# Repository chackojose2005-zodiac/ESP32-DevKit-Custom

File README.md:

# ESP32 Development Kit — Custom PCB Design

> A 4-layer KiCad PCB clone of the Espressif ESP32-DevKitC-v4, designed from the official reference schematic.

---

## Table of Contents

- [Overview](#overview)
- [Board Specifications](#board-specifications)
- [Schematic & Design Details](#schematic--design-details)
- [Bill of Materials (BOM)](#bill-of-materials-bom)
- [Layer Stack-Up](#layer-stack-up)
- [Repository Structure](#repository-structure)
- [How to Open in KiCad](#how-to-open-in-kicad)
- [How to Order the PCB](#how-to-order-the-pcb)
- [Design Notes & Customizations](#design-notes--customizations)
- [References](#references)
- [Author](#author)

---

## Overview

This project is a custom clone of the **Espressif ESP32-DevKitC-v4** development board, designed entirely in **KiCad**. The design is based on the official Espressif reference schematic and layout, with minor modifications for ease of hand assembly.

The board features:
- **ESP32-WROOM-32D** module with integrated PCB antenna
- **CP2102N** USB-to-UART bridge for serial programming
- **AMS1117-3.3** LDO voltage regulator (3.3 V output)
- **BOOT** and **EN** push buttons
- **2 × 19-pin** header connectors exposing all GPIO pins
- SMD components on both front and back copper layers

**Board Dimensions:** 30.73 mm × 56.90 mm  
**Layer Count:** 4 layers  
**Form Factor:** Matches the original ESP32-DevKitC-v4

---

## Board Specifications

| Parameter            | Value                        |
|----------------------|------------------------------|
| Microcontroller      | ESP32-WROOM-32D              |
| USB-UART Bridge      | CP2102N-A01-GQFN28           |
| Voltage Regulator    | AMS1117-3.3 (SOT-223)        |
| Input Voltage        | 5 V via Micro-USB            |
| Output Voltage       | 3.3 V regulated              |
| GPIO Headers         | 2 × 19-pin, 2.54 mm pitch    |
| Board Layers         | 4 (Signal / Signal / Signal / Signal) |
| Board Dimensions     | 30.73 mm × 56.90 mm          |
| Component Standard   | SMD (0402 / 0603 packages)   |
| KiCad Version        | KiCad 7 / 8                  |

---

## Schematic & Design Details

The schematic is organized into **five functional blocks**, mirroring the Espressif reference design:

1. **Power Supply** — Micro-USB input → AMS1117-3.3 LDO → 3.3 V rail with decoupling capacitors
2. **USB / USB-UART** — CP2102N bridge with ESD protection diodes (D4, D5, D6) and auto-reset circuit
3. **ESP32 Module** — ESP32-WROOM-32D with all GPIO broken out to headers
4. **Switch Buttons** — BOOT (GPIO0) and EN (chip enable) with RC debounce networks
5. **Connectors** — J2 and J3 (2 × 19-pin headers)

The auto-reset circuit uses two **MMSS8050** NPN transistors (Q1, Q2) driven by the CP2102N's RTS and DTR lines. This allows the Arduino IDE and `esptool.py` to reset and flash the ESP32 without pressing buttons manually.

---

## Bill of Materials (BOM)

| Reference              | Value              | Footprint                                      |
|------------------------|--------------------|------------------------------------------------|
| C1, C2, C21            | 22 µF / 10 V (20%) | Capacitor_SMD:C_0201_0603Metric                |
| C9, C14, C19, C22      | 0.1 µF / 50 V (10%)| Capacitor_SMD:C_01005_0402Metric               |
| C15                    | 0.1 µF / 50 V (NC) | Capacitor_SMD:C_01005_0402Metric               |
| C20                    | 4.7 µF / 6.3 V     | Capacitor_SMD:C_01005_0402Metric               |
| D1                     | LED                | LED_SMD:LED_0603_1608Metric                    |
| D3                     | Schottky Diode     | Diode_SMD:D_SOD-323                            |
| D4, D5, D6             | TVS Diode          | Diode_SMD:D_SOD-523                            |
| J1                     | USB Micro-B        | Connector_USB:USB_MicroAB_Molex_47590-0001     |
| J2, J3                 | 19-pin Male Header | Connector_PinHeader_2.54mm:PinHeader_1x19_...  |
| MOD1                   | ESP32-WROOM-32D    | ESP32-WROOM32D.pretty:ESP32-WROOM-32D          |
| Q1, Q2                 | MMSS8050-H-TP      | digikey-footprints:SOT-23-3                    |
| R2, R24                | 2 KΩ (5%)          | Resistor_SMD:R_01005_0402Metric                |
| R7, R18                | 0 Ω (5%)           | Resistor_SMD:R_01005_0402Metric                |
| R11, R21, R22          | 10 KΩ (5%)         | Resistor_SMD:R_01005_0402Metric                |
| R23                    | 10 KΩ (NC)         | Resistor_SMD:R_01005_0402Metric                |
| R25                    | 22.1 KΩ (5%)       | Resistor_SMD:R_01005_0402Metric                |
| R26                    | 47.5 KΩ (5%)       | Resistor_SMD:R_01005_0402Metric                |
| SW1, SW2               | Push Button        | Button_Switch_SMD:SW_SPST_B3S-1000             |
| U1                     | CP2102N-A01-GQFN28 | Package_DFN_QFN:TQFN-28-1EP_5x5mm_P0.5mm      |
| U2                     | AMS1117-3.3        | Package_TO_SOT_SMD:SOT-223-3_TabPin2           |

> **(NC)** = Not Connected / DNP (Do Not Populate)

---

## Layer Stack-Up

| Layer      | KiCad Name   | Purpose                     |
|------------|--------------|-----------------------------|
| Layer 1    | F.Cu         | Signal routing (top)        |
| Layer 2    | In1.Cu       | Signal routing (inner 1)    |
| Layer 3    | In2.Cu       | Signal routing (inner 2)    |
| Layer 4    | B.Cu         | Signal routing (bottom)     |

All four copper layers are used for **signal routing**. Power (VCC/3.3 V) and ground (GND) connections are routed as **copper tracks** across all layers using KiCad's **autorouter**, rather than as dedicated power or ground planes. This approach was used to complete all 68 nets with 0 unrouted connections.

> **Note:** In a production design, dedicated inner ground and power planes (In1.Cu = GND, In2.Cu = PWR) are recommended for better RF performance and signal integrity. For this educational clone, autorouted tracks on all four layers achieve full connectivity.

---

## Repository Structure

```
ESP32-DevKit-Custom/
│
├── ESP32-DevKit-Custom.kicad_pro    # KiCad project file
├── ESP32-DevKit-Custom.kicad_sch    # Schematic
├── ESP32-DevKit-Custom.kicad_pcb    # PCB layout
│
├── ESP32-WROOM32D.pretty/           # Custom ESP32-WROOM-32D footprint
├── CP2102N-A01-GQFN28footprint.pretty/ # Custom CP2102N footprint
├── MMSS8050-H-TPfootprint.pretty/   # Custom MMSS8050 footprint
│
├── Gerbers/                         # Manufacturing files
│   ├── ESP32-DevKit-F_Cu.gtl
│   ├── ESP32-DevKit-In1_Cu.g2
│   ├── ESP32-DevKit-In2_Cu.g3
│   ├── ESP32-DevKit-B_Cu.gbl
│   ├── ESP32-DevKit-F_Mask.gts
│   ├── ESP32-DevKit-B_Mask.gbs
│   ├── ESP32-DevKit-F_Silkscreen.gto
│   ├── ESP32-DevKit-B_Silkscreen.gbo
│   ├── ESP32-DevKit-Edge_Cuts.gm1
│   └── ESP32-DevKit-drill.drl
│
├── BOM/
│   └── ESP32-DevKit-BOM.csv         # Bill of materials
│
├── 3D/
│   └── ESP32-DevKit-3D.png          # 3D render screenshot
│
└── README.md
```

---

## How to Open in KiCad

### Prerequisites

- [KiCad 7 or later](https://www.kicad.org/download/) installed
- Internet connection (to download symbol/footprint libraries if missing)

### Steps

1. **Clone this repository:**
   ```bash
   git clone https://github.com/chackojose2005-zodiac/ESP32-DevKit-Custom.git
   cd ESP32-DevKit-Custom
   ```

2. **Open KiCad:**
   Launch KiCad and click **File → Open Project**, then select `ESP32-DevKit-Custom.kicad_pro`.

3. **Open the Schematic:**
   In the KiCad project manager, double-click **Schematic Editor** (`.kicad_sch`) to view the schematic.

4. **Open the PCB Layout:**
   Double-click **PCB Editor** (`.kicad_pcb`) to open the board layout.

5. **Verify the 3D View:**
   In the PCB Editor, go to **View → 3D Viewer** to see the 3D render of the board.

6. **Run DRC (Design Rule Check):**
   In the PCB Editor, go to **Inspect → Design Rules Checker** and click **Run DRC** to verify the design.

---

## How to Order the PCB

### Generating Gerber Files (if not already included)

1. Open the PCB in KiCad PCB Editor.
2. Go to **File → Fabrication Outputs → Gerbers (.gbr)**.
3. Select all layers (F.Cu, In1.Cu, In2.Cu, B.Cu, F.Mask, B.Mask, F.Silkscreen, B.Silkscreen, Edge.Cuts).
4. Click **Plot**.
5. Also generate drill files: **File → Fabrication Outputs → Drill Files (.drl)**.
6. Zip the entire `Gerbers/` folder.

### Ordering from JLCPCB (Recommended)

1. Go to [jlcpcb.com](https://jlcpcb.com) and click **Order Now**.
2. Upload the zipped Gerber files.
3. Set the following options:
   - **Layers:** 4
   - **Dimensions:** Auto-detected (~30.73 × 56.90 mm)
   - **PCB Quantity:** 5 (minimum)
   - **Surface Finish:** HASL (lead-free) or ENIG
   - **Copper Weight:** 1 oz
4. Review the board preview, then proceed to checkout.

> **Note:** 4-layer boards cost slightly more than 2-layer boards. JLCPCB's 4-layer pricing starts from around $2–5 per board for small quantities.

---

## Design Notes & Customizations

This design is faithful to the Espressif ESP32-DevKitC-v4 reference, with the following intentional modifications:

- **ESP32-WROOM-32D module used** — The design uses the ESP32-WROOM-32D variant with a custom footprint, featuring a single rectangular SMD thermal pad (pad 39) for GND instead of individual through-hole vias.

- **Autorouted PCB layout** — All nets (GND, 3.3 V, signals) are connected using KiCad's autorouter across all four copper layers (F.Cu, In1.Cu, In2.Cu, B.Cu). The result is **0 unrouted connections** across all 68 nets.

- **Voltage regulator (U2 / AMS1117-3.3) placed on the back copper layer (B.Cu)** — In the original Espressif reference, the regulator is on the front. Moving it to the back frees up front-side real estate for small passives, making hand-soldering easier.

- **Custom footprints** — The ESP32-WROOM-32D, CP2102N-A01-GQFN28, and MMSS8050-H-TP footprints were created from scratch and are included in the repository as local `.pretty` libraries.

Other design considerations:
- The ESP32's RF antenna extends **outside** the board edge to avoid copper interference with the 2.4 GHz signal.
- TVS diodes (D4, D5, D6) protect the USB data lines against ESD events.
- RC networks on BOOT and EN pins prevent spurious resets due to contact bounce.

---

## References

- [Espressif ESP32-DevKitC-v4 Reference Design](https://www.espressif.com/en/support/documents/technical-documents?keys=ESP32-Devkit) — Official schematics, PCB layout, BOM, and Gerber files
- [ESP32-WROOM-32D Datasheet](https://www.espressif.com/sites/default/files/documentation/esp32-wroom-32d_esp32-wroom-32u_datasheet_en.pdf)
- [CP2102N Datasheet — Silicon Labs](https://www.silabs.com/documents/public/data-sheets/cp2102n-datasheet.pdf)
- [AMS1117-3.3 Datasheet](http://www.advanced-monolithic.com/pdf/ds1117.pdf)
- [KiCad Documentation](https://docs.kicad.org/)

---

## Author

**Chacko Jose**  
B.Tech Electronics & Communication Engineering, Semester 2  
School of Engineering, CUSAT, Kochi  
GitHub: [@chackojose2005-zodiac](https://github.com/chackojose2005-zodiac)

---

*This project was completed as part of Week 4 — Project 6 of the embedded systems PCB design curriculum.*

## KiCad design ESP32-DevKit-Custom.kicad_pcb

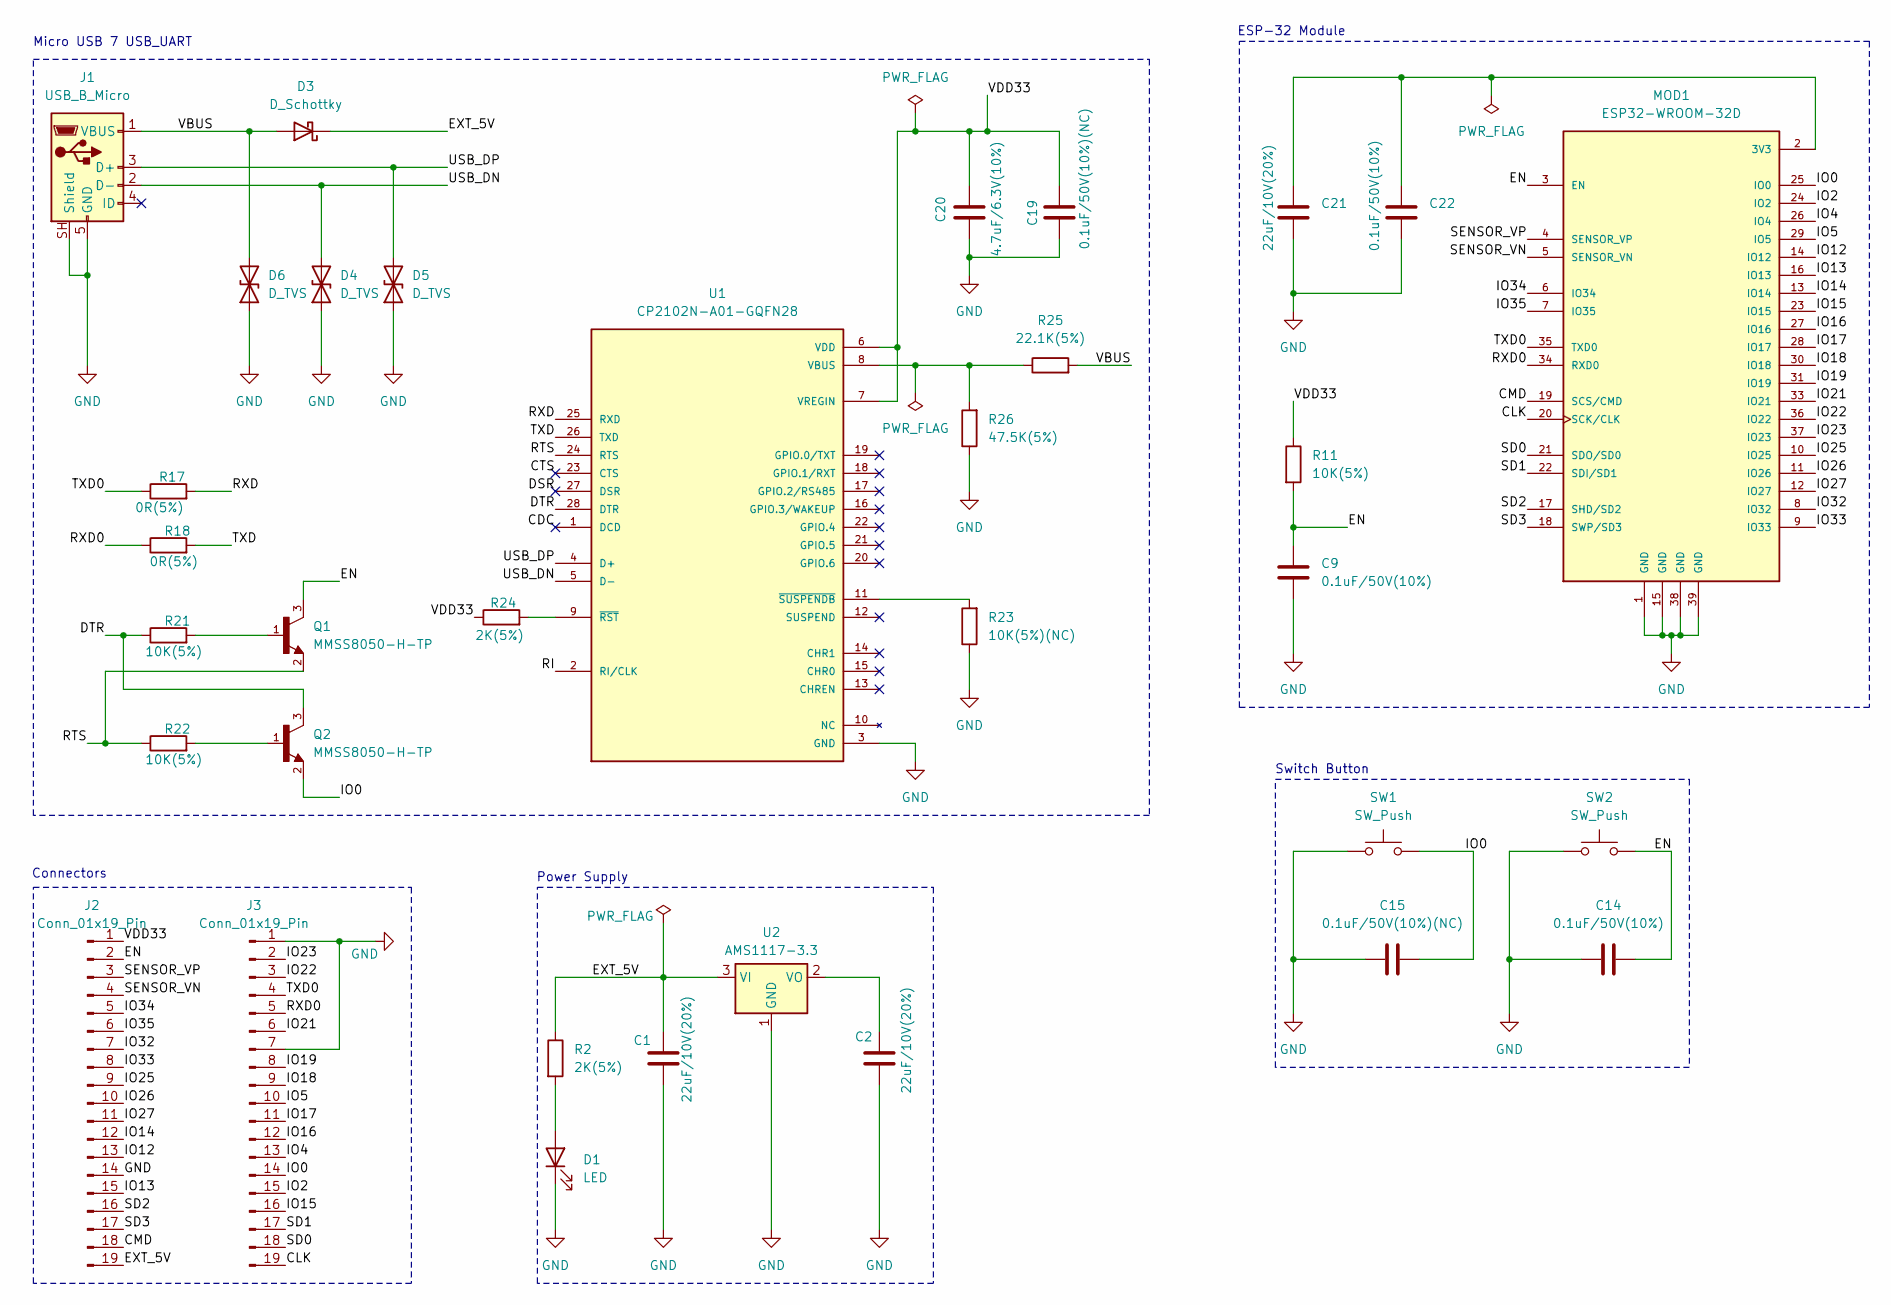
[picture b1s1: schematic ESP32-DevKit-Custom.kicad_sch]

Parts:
C1, C2, C21: 22uF/10V(20%); C_01005_0402Metric
C9, C14, C22: 0.1uF/50V(10%); C_01005_0402Metric
C15, C19: 0.1uF/50V(10%)(NC); C_01005_0402Metric
C20: 4.7uF/6.3V(10%); C_01005_0402Metric
D1: LED; LED_0603_1608Metric
D3: D_Schottky; D_SOD-323
D4, D5, D6: D_TVS; D_SOD-523
J1: USB_B_Micro; USB_Micro-AB_Molex_47590-0001
J2, J3: Conn_01x19_Pin; PinHeader_1x19_P2.54mm_Vertical
MOD1: ESP32-WROOM-32D; MODULE_ESP32-WROOM-32D; PARTREV 1.9
Q1, Q2: MMSS8050-H-TP; TRANS_MMSS8050-H-TP; PARTREV D
R2, R24: 2K(5%); R_01005_0402Metric
R11, R21, R22: 10K(5%); R_01005_0402Metric
R17, R18: 0R(5%); R_01005_0402Metric
R23: 10K(5%)(NC); R_01005_0402Metric
R25: 22.1K(5%); R_01005_0402Metric
R26: 47.5K(5%); R_01005_0402Metric
SW1, SW2: SW_Push; SW_SPST_B3S-1000
U1: CP2102N-A01-GQFN28; QFN50P500X500X80-29N; PARTREV 1.0
U2: AMS1117-3.3; SOT-223-3_TabPin2

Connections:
/CDC: U1.1 (DCD)
/CLK: J3.19, MOD1.20 (SCK/CLK)
/CMD: J2.18, MOD1.19 (SCS/CMD)
/CTS: U1.23 (CTS)
/DSR: U1.27 (DSR)
/DTR: Q2.3, R21.1, U1.28 (DTR)
/EN: C9.1, C14.2, J2.2, MOD1.3 (EN), Q1.3, R11.2, SW2.2
/EXT_5V: C1.1, D3.1 (K), J2.19, R2.1, U2.3 (VI)
/IO0: C15.2, J3.14, MOD1.25 (IO0), Q2.2, SW1.2
/IO2: J3.15, MOD1.24 (IO2)
/IO4: J3.13, MOD1.26 (IO4)
/IO5: J3.10, MOD1.29 (IO5)
/IO12: J2.13, MOD1.14 (IO12)
/IO13: J2.15, MOD1.16 (IO13)
/IO14: J2.12, MOD1.13 (IO14)
/IO15: J3.16, MOD1.23 (IO15)
/IO16: J3.12, MOD1.27 (IO16)
/IO17: J3.11, MOD1.28 (IO17)
/IO18: J3.9, MOD1.30 (IO18)
/IO19: J3.8, MOD1.31 (IO19)
/IO21: J3.6, MOD1.33 (IO21)
/IO22: J3.3, MOD1.36 (IO22)
/IO23: J3.2, MOD1.37 (IO23)
/IO25: J2.9, MOD1.10 (IO25)
/IO26: J2.10, MOD1.11 (IO26)
/IO27: J2.11, MOD1.12 (IO27)
/IO32: J2.7, MOD1.8 (IO32)
/IO33: J2.8, MOD1.9 (IO33)
/IO34: J2.5, MOD1.6 (IO34)
/IO35: J2.6, MOD1.7 (IO35)
/RI: U1.2 (RI/CLK)
/RTS: Q1.2, R22.1, U1.24 (RTS)
/RXD: R17.2, U1.25 (RXD)
/RXD0: J3.5, MOD1.34 (RXD0), R18.1
/SD0: J3.18, MOD1.21 (SDO/SD0)
/SD1: J3.17, MOD1.22 (SDI/SD1)
/SD2: J2.16, MOD1.17 (SHD/SD2)
/SD3: J2.17, MOD1.18 (SWP/SD3)
/SENSOR_VN: J2.4, MOD1.5 (SENSOR_VN)
/SENSOR_VP: J2.3, MOD1.4 (SENSOR_VP)
/TXD: R18.2, U1.26 (TXD)
/TXD0: J3.4, MOD1.35 (TXD0), R17.1
/USB_DN: D4.2 (A2), J1.2 (D-), U1.5 (D-)
/USB_DP: D5.2 (A2), J1.3 (D+), U1.4 (D+)
/VBUS: D3.2 (A), D6.2 (A2), J1.1 (VBUS), R25.2
/VDD33: C19.1, C20.1, J2.1, R11.1, R24.1, U1.6 (VDD), U1.7 (VREGIN)
GND: C1.2, C2.2, C9.2, C14.1, C15.1, C19.2, C20.2, C21.2, C22.2, D1.1 (K), D4.1 (A1), D5.1 (A1), D6.1 (A1), J1.5 (GND), J1.SH (Shield), J2.14, J3.1, J3.7, MOD1.1 (GND), MOD1.15 (GND), MOD1.38 (GND), MOD1.39 (GND), MOD1.39_1 (GND), MOD1.39_2 (GND), MOD1.39_3 (GND), MOD1.39_4 (GND), MOD1.39_5 (GND), MOD1.39_6 (GND), MOD1.39_7 (GND), MOD1.39_8 (GND), MOD1.39_9 (GND), MOD1.39_10 (GND), MOD1.39_11 (GND), MOD1.39_12 (GND), MOD1.39_13 (GND), MOD1.39_14 (GND), MOD1.39_15 (GND), MOD1.39_16 (GND), MOD1.39_17 (GND), MOD1.39_18 (GND), MOD1.39_19 (GND), MOD1.39_20 (GND), MOD1.39_21 (GND), R23.1, R26.1, SW1.1, SW2.1, U1.3 (GND), U1.29 (GND), U2.1 (GND)
unnamed: D1.2 (A), R2.2
unnamed: C21.1, C22.1, MOD1.2 (3V3)
unnamed: Q1.1, R21.2
unnamed: Q2.1, R22.2
unnamed: R25.1, R26.2, U1.8 (VBUS)
unnamed: R24.2, U1.9 (~RST)
unnamed: R23.2, U1.11 (~SUSPENDB)
unnamed: C2.1, U2.2 (VO)

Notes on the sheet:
Connectors
Switch Button
ESP-32 Module
Micro USB 7 USB_UART
Power Supply

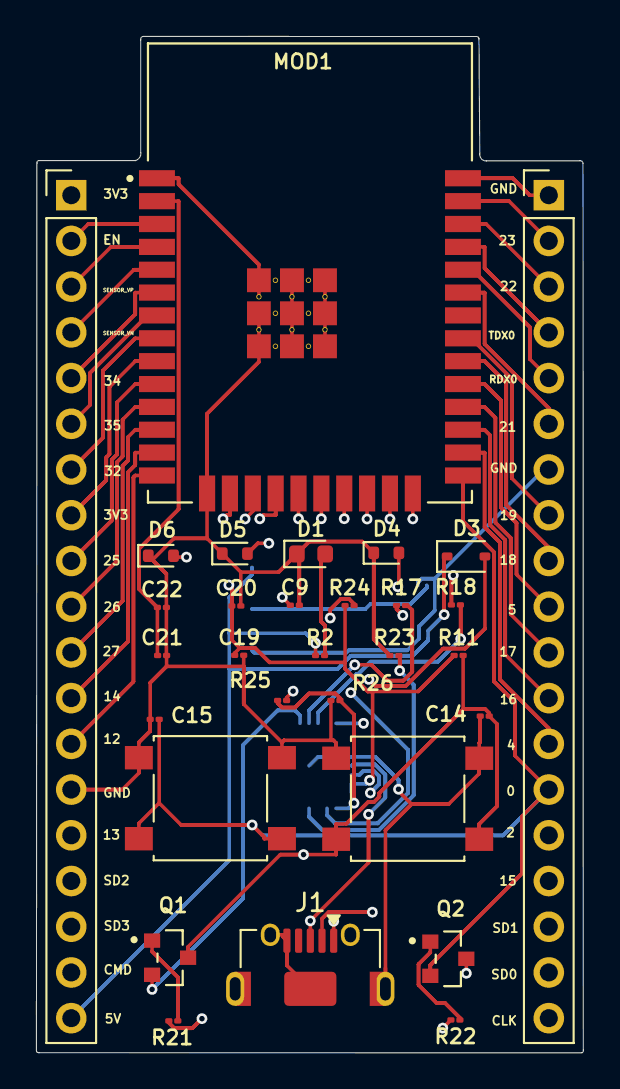
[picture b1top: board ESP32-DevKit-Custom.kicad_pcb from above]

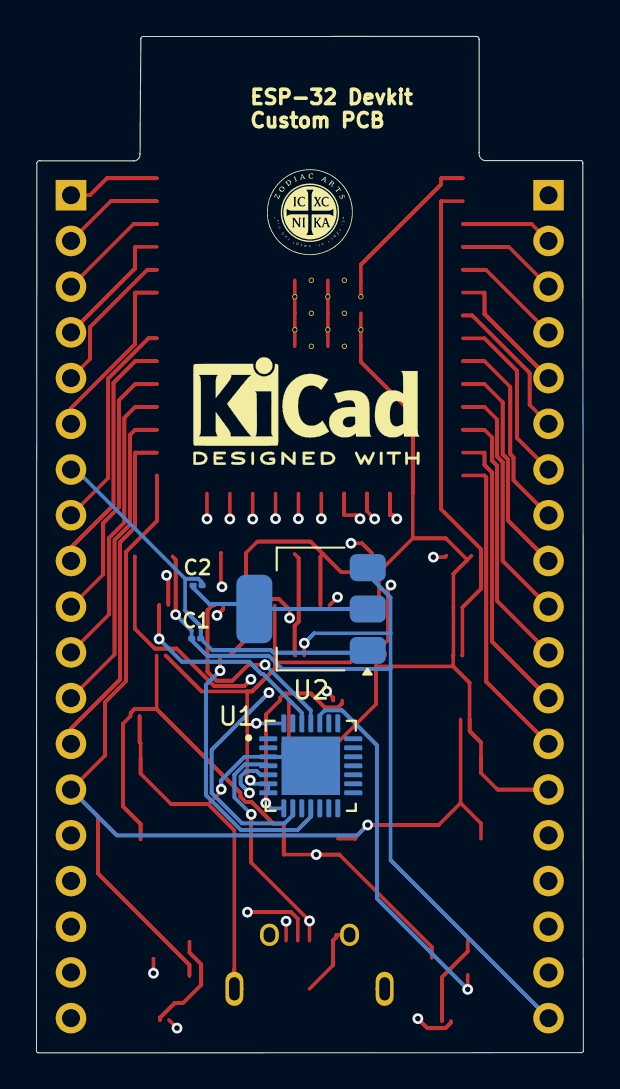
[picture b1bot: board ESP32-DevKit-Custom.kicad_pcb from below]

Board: 4 copper layers, 30.4 x 56.5 mm, 34 parts (4 on the bottom side), 51 nets.

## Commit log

2026-06-26 Add README
2026-06-26 Add completed schematic
2026-06-27 Update ESP_32 Schematic
2026-06-28 Add README for ESP32-DevKit-Custom PCB project
2026-06-28 Rename README (1).md to README.md
2026-06-28 Add final PCB layout and footprints
2026-06-28 Add Gerber and drill files for fabrication
2026-06-28 Add Bill of Materials (BOM)
